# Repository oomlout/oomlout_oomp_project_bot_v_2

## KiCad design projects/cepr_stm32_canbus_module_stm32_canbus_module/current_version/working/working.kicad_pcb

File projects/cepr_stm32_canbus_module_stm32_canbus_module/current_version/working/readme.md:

# stm32_canbus_module
 
## summary 
* id: cepr_stm32_canbus_module_stm32_canbus_module
* user: cepr
* name: stm32_canbus_module
* board: stm32_canbus_module
* repo: https://github.com/cepr/stm32-canbus-module
* src_file_repo_kicad_pcb: stm32_canbus_module.kicad_pcb
* src_file_repo_kicad_pcb_link: https://github.com/cepr/stm32-canbus-module/tree/master/stm32_canbus_module.kicad_pcb
* src_file_repo_kicad_sch: stm32_canbus_module.kicad_sch
* src_file_repo_kicad_sch_link: https://github.com/cepr/stm32-canbus-module/tree/master/stm32_canbus_module.kicad_sch

* src_file_repo_sch: 
* src_file_repo_sch_link: https://github.com/cepr/stm32-canbus-module/tree/master/
* full details link: https://github.com/oomlout/oomlout_oomp_project_bot_v_2/tree/main/projects/cepr_stm32_canbus_module_stm32_canbus_module/current_version/working

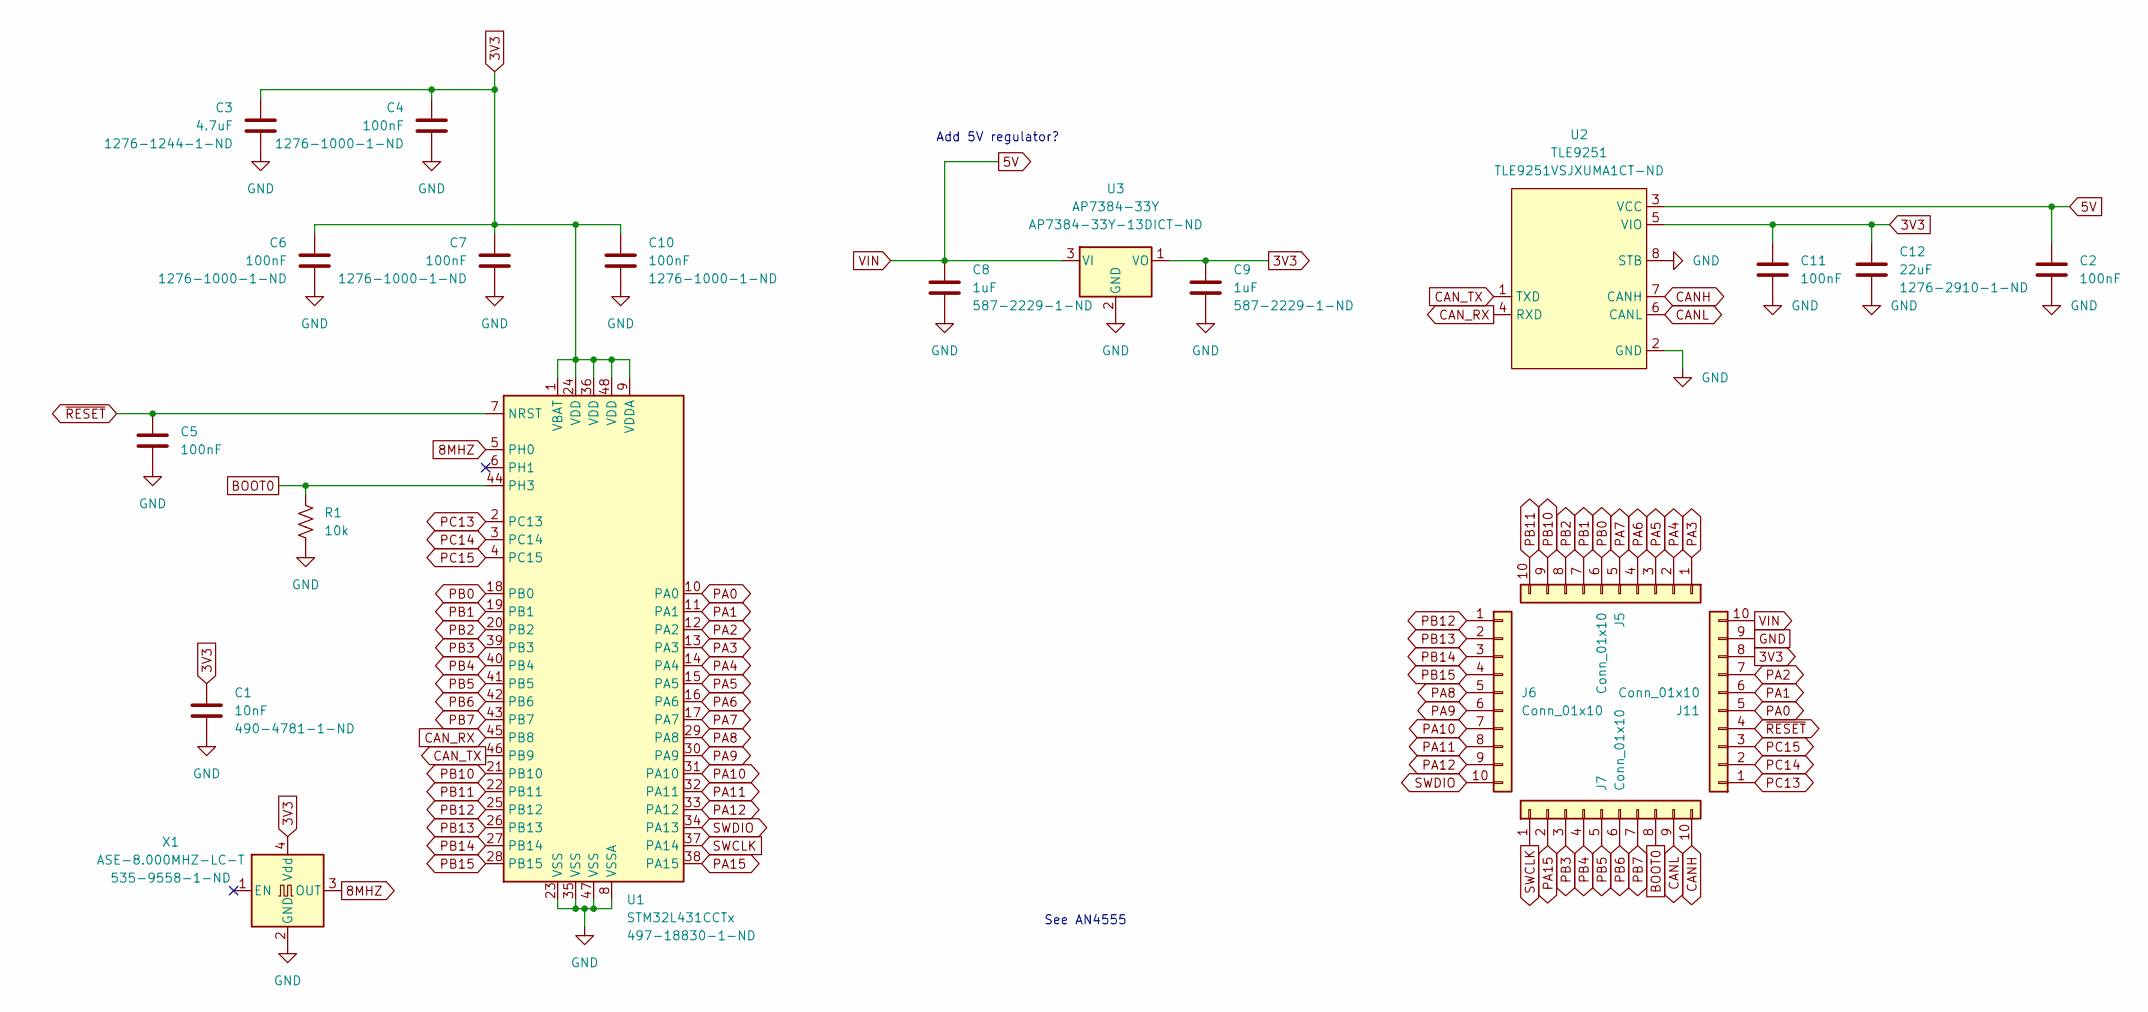
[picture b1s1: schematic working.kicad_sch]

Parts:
C1: 10nF; C_0603_1608Metric_Pad1.08x0.95mm_HandSolder; DigiKey 490-4781-1-ND
C2, C4, C5, C6, C7, C10, C11: 100nF; C_0603_1608Metric_Pad1.08x0.95mm_HandSolder; DigiKey 1276-1000-1-ND
C3: 4.7uF; C_0805_2012Metric_Pad1.18x1.45mm_HandSolder; DigiKey 1276-1244-1-ND
C8, C9: 1uF; C_0805_2012Metric_Pad1.18x1.45mm_HandSolder; DigiKey 587-2229-1-ND
C12: 22uF; C_0805_2012Metric_Pad1.18x1.45mm_HandSolder; DigiKey 1276-2910-1-ND
J5, J6, J7, J11: Conn_01x10; PinHeader_1x10_P2.54mm_Vertical
R1: 10k; R_0603_1608Metric_Pad0.98x0.95mm_HandSolder; DigiKey RNCP0603FTD10K0CT-ND
U1: STM32L431CCTx; LQFP-48_7x7mm_P0.5mm; DigiKey 497-18830-1-ND
U2: TLE9251; SOIC-8_3.9x4.9mm_P1.27mm; DigiKey TLE9251VSJXUMA1CT-ND
U3: AP7384-33Y; SOT-89-3; DigiKey AP7384-33Y-13DICT-ND
X1: ASE-8.000MHZ-LC-T; Oscillator_SMD_Abracon_ASE-4Pin_3.2x2.5mm_HandSoldering; DigiKey 535-9558-1-ND

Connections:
3V3: C1.1, C3.1, C4.1, C6.1, C7.1, C9.1, C10.1, C11.1, C12.1, J11.8, U1.1 (VBAT), U1.9 (VDDA), U1.24 (VDD), U1.36 (VDD), U1.48 (VDD), U2.5 (VIO), U3.1 (VO), X1.4 (Vdd)
5V: C2.1, C8.1, J11.10, U2.3 (VCC), U3.3 (VI)
8MHZ: U1.5 (PH0), X1.3 (OUT)
BOOT0: J7.8, R1.2, U1.44 (PH3)
CANH: J7.10, U2.7 (CANH)
CANL: J7.9, U2.6 (CANL)
CAN_RX: U1.45 (PB8), U2.4 (RXD)
CAN_TX: U1.46 (PB9), U2.1 (TXD)
GND: C1.2, C2.2, C3.2, C4.2, C5.2, C6.2, C7.2, C8.2, C9.2, C10.2, C11.2, C12.2, J11.9, R1.1, U1.8 (VSSA), U1.23 (VSS), U1.35 (VSS), U1.47 (VSS), U2.2 (GND), U2.8 (STB), U3.2 (GND), X1.2 (GND)
PA0: J11.5, U1.10 (PA0)
PA1: J11.6, U1.11 (PA1)
PA2: J11.7, U1.12 (PA2)
PA3: J5.1, U1.13 (PA3)
PA4: J5.2, U1.14 (PA4)
PA5: J5.3, U1.15 (PA5)
PA6: J5.4, U1.16 (PA6)
PA7: J5.5, U1.17 (PA7)
PA8: J6.5, U1.29 (PA8)
PA9: J6.6, U1.30 (PA9)
PA10: J6.7, U1.31 (PA10)
PA11: J6.8, U1.32 (PA11)
PA12: J6.9, U1.33 (PA12)
PA15: J7.2, U1.38 (PA15)
PB0: J5.6, U1.18 (PB0)
PB1: J5.7, U1.19 (PB1)
PB2: J5.8, U1.20 (PB2)
PB3: J7.3, U1.39 (PB3)
PB4: J7.4, U1.40 (PB4)
PB5: J7.5, U1.41 (PB5)
PB6: J7.6, U1.42 (PB6)
PB7: J7.7, U1.43 (PB7)
PB10: J5.9, U1.21 (PB10)
PB11: J5.10, U1.22 (PB11)
PB12: J6.1, U1.25 (PB12)
PB13: J6.2, U1.26 (PB13)
PB14: J6.3, U1.27 (PB14)
PB15: J6.4, U1.28 (PB15)
PC13: J11.1, U1.2 (PC13)
PC14: J11.2, U1.3 (PC14)
PC15: J11.3, U1.4 (PC15)
SWCLK: J7.1, U1.37 (PA14)
SWDIO: J6.10, U1.34 (PA13)
~RESET: C5.1, J11.4, U1.7 (NRST)

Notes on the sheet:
Add 5V regulator?
See AN4555

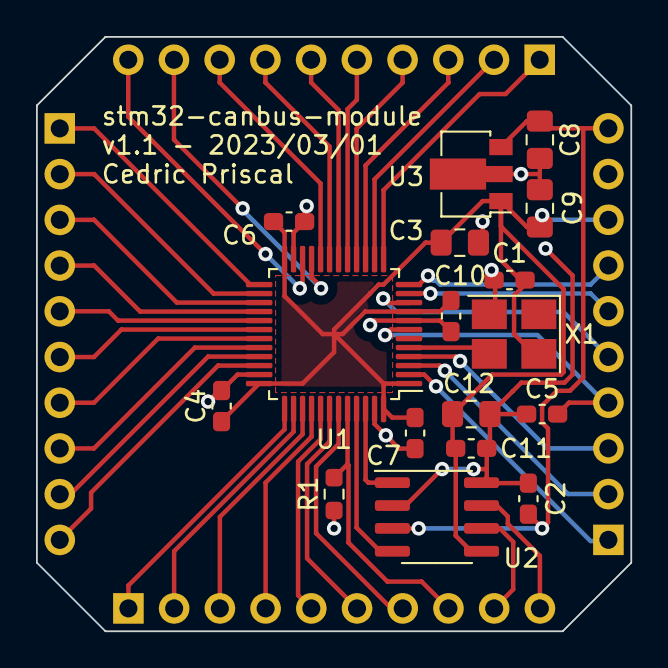
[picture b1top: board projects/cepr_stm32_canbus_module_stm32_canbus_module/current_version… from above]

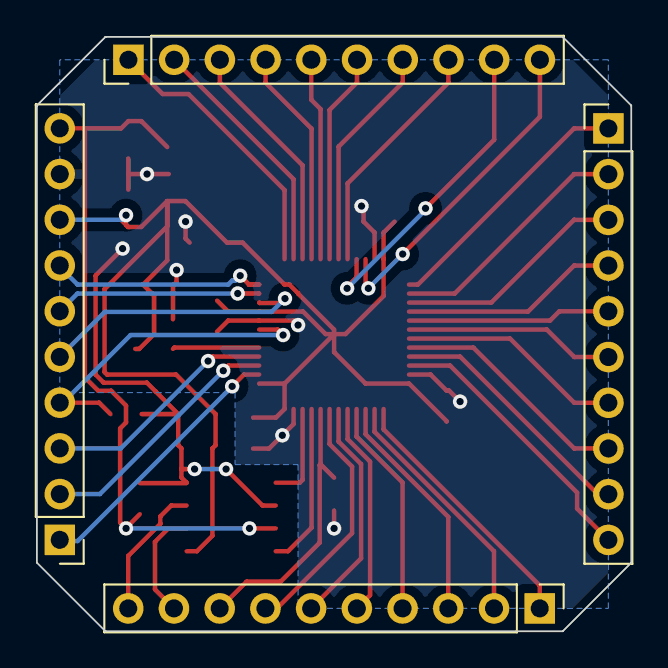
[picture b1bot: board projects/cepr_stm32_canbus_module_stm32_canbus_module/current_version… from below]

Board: 2 copper layers, 33.0 x 33.0 mm, 21 parts (4 on the bottom side), 43 nets.

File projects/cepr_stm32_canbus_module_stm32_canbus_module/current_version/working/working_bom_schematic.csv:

"Source:","C:\gh\oomlout_oomp_project_bot_v_2\projects\cepr_stm32_canbus_module_stm32_canbus_module\current_version\working\working.kicad_sch"
"Date:","28/09/2023 19:39:32"
"Tool:","Eeschema 7.0.6"
"Generator:","C:/Program Files/KiCad/7.0/bin/scripting/plugins/bom_csv_grouped_by_value_with_fp.py"
"Component Count:","21"
"Ref","Qnty","Value","Cmp name","Footprint","Description","Vendor","DNP"
"C1","1","10nF","C","Capacitor_SMD:C_0603_1608Metric_Pad1.08x0.95mm_HandSolder","Unpolarized capacitor","",""
"C2, C4, C5, C6, C7, C10, C11","7","100nF","C","Capacitor_SMD:C_0603_1608Metric_Pad1.08x0.95mm_HandSolder","Unpolarized capacitor","",""
"C3","1","4.7uF","C","Capacitor_SMD:C_0805_2012Metric_Pad1.18x1.45mm_HandSolder","Unpolarized capacitor","",""
"C8, C9","2","1uF","C","Capacitor_SMD:C_0805_2012Metric_Pad1.18x1.45mm_HandSolder","Unpolarized capacitor","",""
"C12","1","22uF","C","Capacitor_SMD:C_0805_2012Metric_Pad1.18x1.45mm_HandSolder","Unpolarized capacitor","",""
"J5, J6, J7, J11","4","Conn_01x10","Conn_01x10","Connector_PinHeader_2.54mm:PinHeader_1x10_P2.54mm_Vertical","Generic connector, single row, 01x10, script generated (kicad-library-utils/schlib/autogen/connector/)","",""
"R1","1","10k","R_US","Resistor_SMD:R_0603_1608Metric_Pad0.98x0.95mm_HandSolder","Resistor, US symbol","",""
"U1","1","STM32L431CCTx","STM32L431CCTx","Package_QFP:LQFP-48_7x7mm_P0.5mm","ARM Cortex-M4 MCU, 256KB flash, 64KB RAM, 80MHz, 1.71-3.6V, 38 GPIO, LQFP-48","",""
"U2","1","TLE9251","TLE9251","Package_SO:SOIC-8_3.9x4.9mm_P1.27mm","","",""
"U3","1","AP7384-33Y","AP7384-28Y","Package_TO_SOT_SMD:SOT-89-3","50mA Low Dropout Voltage Regulator, Fixed Output 2.8V, Wide Input Voltage Range 40V, SOT-89-3","",""
"X1","1","ASE-8.000MHZ-LC-T","ASE-xxxMHz","Oscillator:Oscillator_SMD_Abracon_ASE-4Pin_3.2x2.5mm_HandSoldering","3.3V CMOS SMD Crystal Clock Oscillator, Abracon","",""

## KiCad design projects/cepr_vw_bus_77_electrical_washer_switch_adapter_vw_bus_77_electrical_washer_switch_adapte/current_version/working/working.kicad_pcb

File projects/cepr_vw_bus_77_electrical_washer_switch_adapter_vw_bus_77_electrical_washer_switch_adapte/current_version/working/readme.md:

# vw_bus_77_electrical_washer_switch_adapter
 
## summary 
* id: cepr_vw_bus_77_electrical_washer_switch_adapter_vw_bus_77_electrical_washer_switch_adapte
* user: cepr
* name: vw_bus_77_electrical_washer_switch_adapter
* board: vw_bus_77_electrical_washer_switch_adapte
* repo: https://github.com/cepr/vw-bus-77-electrical-washer-switch-adapter
* src_file_repo_kicad_pcb: vw-bus-77-electrical-washer-switch-adapte.kicad_pcb
* src_file_repo_kicad_pcb_link: https://github.com/cepr/vw-bus-77-electrical-washer-switch-adapter/tree/master/vw-bus-77-electrical-washer-switch-adapte.kicad_pcb

* src_file_repo_sch: vw-bus-77-electrical-washer-switch-adapte.sch
* src_file_repo_sch_link: https://github.com/cepr/vw-bus-77-electrical-washer-switch-adapter/tree/master/vw-bus-77-electrical-washer-switch-adapte.sch
* full details link: https://github.com/oomlout/oomlout_oomp_project_bot_v_2/tree/main/projects/cepr_vw_bus_77_electrical_washer_switch_adapter_vw_bus_77_electrical_washer_switch_adapte/current_version/working

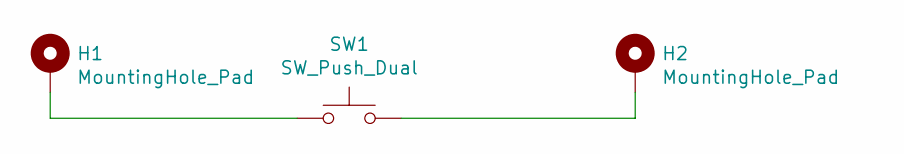
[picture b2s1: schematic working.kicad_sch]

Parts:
H1, H2: MountingHole_Pad; MountingHole_3.2mm_M3_Pad_Via
SW1: SW_Push_Dual; SW_PUSH_6mm

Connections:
unnamed: H1.1, SW1.1
unnamed: H2.1, SW1.2

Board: 2 copper layers, 3 parts (0 on the bottom side), 2 nets, no tracks yet.

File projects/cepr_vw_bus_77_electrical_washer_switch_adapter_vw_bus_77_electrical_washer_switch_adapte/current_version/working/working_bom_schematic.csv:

"Source:","C:\gh\oomlout_oomp_project_bot_v_2\projects\cepr_vw_bus_77_electrical_washer_switch_adapter_vw_bus_77_electrical_washer_switch_adapte\current_version\working\working.kicad_sch"
"Date:","28/09/2023 19:47:27"
"Tool:","Eeschema 7.0.6"
"Generator:","C:/Program Files/KiCad/7.0/bin/scripting/plugins/bom_csv_grouped_by_value_with_fp.py"
"Component Count:","3"
"Ref","Qnty","Value","Cmp name","Footprint","Description","Vendor","DNP"
"H1, H2","2","MountingHole_Pad","MountingHole_Pad","MountingHole:MountingHole_3.2mm_M3_Pad_Via","Mounting Hole with connection","",""
"SW1","1","SW_Push_Dual","SW_Push","Button_Switch_THT:SW_PUSH_6mm","Push button switch, generic, two pins","",""

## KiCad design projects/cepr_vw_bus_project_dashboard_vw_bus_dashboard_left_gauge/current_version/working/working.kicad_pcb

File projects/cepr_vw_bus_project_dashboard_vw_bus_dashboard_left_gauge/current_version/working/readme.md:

# vw_bus_project_dashboard
 
## summary 
* id: cepr_vw_bus_project_dashboard_vw_bus_dashboard_left_gauge
* user: cepr
* name: vw_bus_project_dashboard
* board: vw_bus_dashboard_left_gauge
* repo: https://github.com/cepr/vw-bus-project-dashboard
* src_file_repo_kicad_pcb: kicad/vw_bus_dashboard_left_gauge.kicad_pcb
* src_file_repo_kicad_pcb_link: https://github.com/cepr/vw-bus-project-dashboard/tree/master/kicad/vw_bus_dashboard_left_gauge.kicad_pcb

* src_file_repo_sch: kicad/vw_bus_dashboard_left_gauge.sch
* src_file_repo_sch_link: https://github.com/cepr/vw-bus-project-dashboard/tree/master/kicad/vw_bus_dashboard_left_gauge.sch
* full details link: https://github.com/oomlout/oomlout_oomp_project_bot_v_2/tree/main/projects/cepr_vw_bus_project_dashboard_vw_bus_dashboard_left_gauge/current_version/working

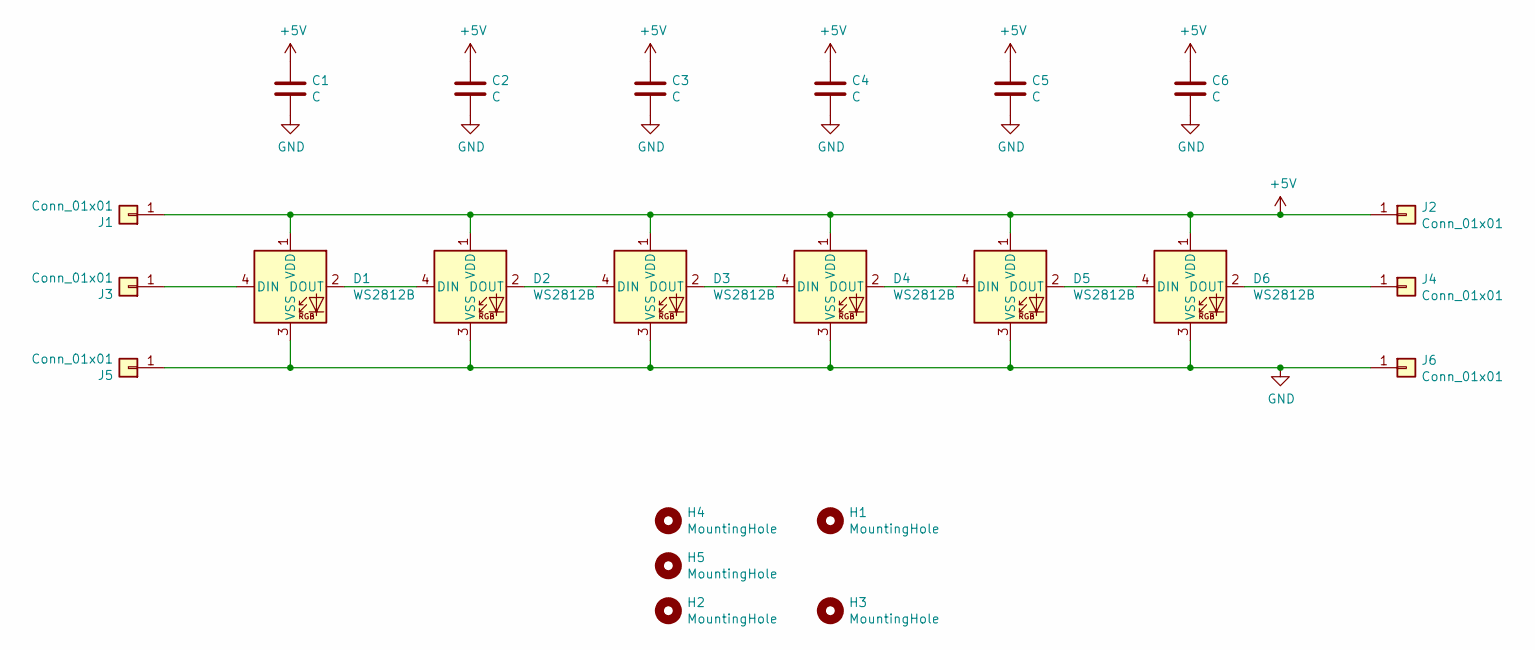
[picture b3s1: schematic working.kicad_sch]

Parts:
C1, C2, C3, C4, C5, C6: C; C_0603_1608Metric
D1, D2, D3, D4, D5, D6: WS2812B; LED_WS2812B_PLCC4_5.0x5.0mm_P3.2mm
H1, H3: MountingHole; MountingHole_5.3mm_M5
H2, H4, H5: MountingHole; MountingHole_3.2mm_M3
J1, J2, J3, J4, J5, J6: Conn_01x01; SolderWirePad_1x01_SMD_5x10mm

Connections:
+5V: C1.1, C2.1, C3.1, C4.1, C5.1, C6.1, D1.1 (VDD), D2.1 (VDD), D3.1 (VDD), D4.1 (VDD), D5.1 (VDD), D6.1 (VDD), J1.1, J2.1
GND: C1.2, C2.2, C3.2, C4.2, C5.2, C6.2, D1.3 (VSS), D2.3 (VSS), D3.3 (VSS), D4.3 (VSS), D5.3 (VSS), D6.3 (VSS), J5.1, J6.1
unnamed: D1.2 (DOUT), D2.4 (DIN)
unnamed: D1.4 (DIN), J3.1
unnamed: D2.2 (DOUT), D3.4 (DIN)
unnamed: D3.2 (DOUT), D4.4 (DIN)
unnamed: D4.2 (DOUT), D5.4 (DIN)
unnamed: D5.2 (DOUT), D6.4 (DIN)
unnamed: D6.2 (DOUT), J4.1

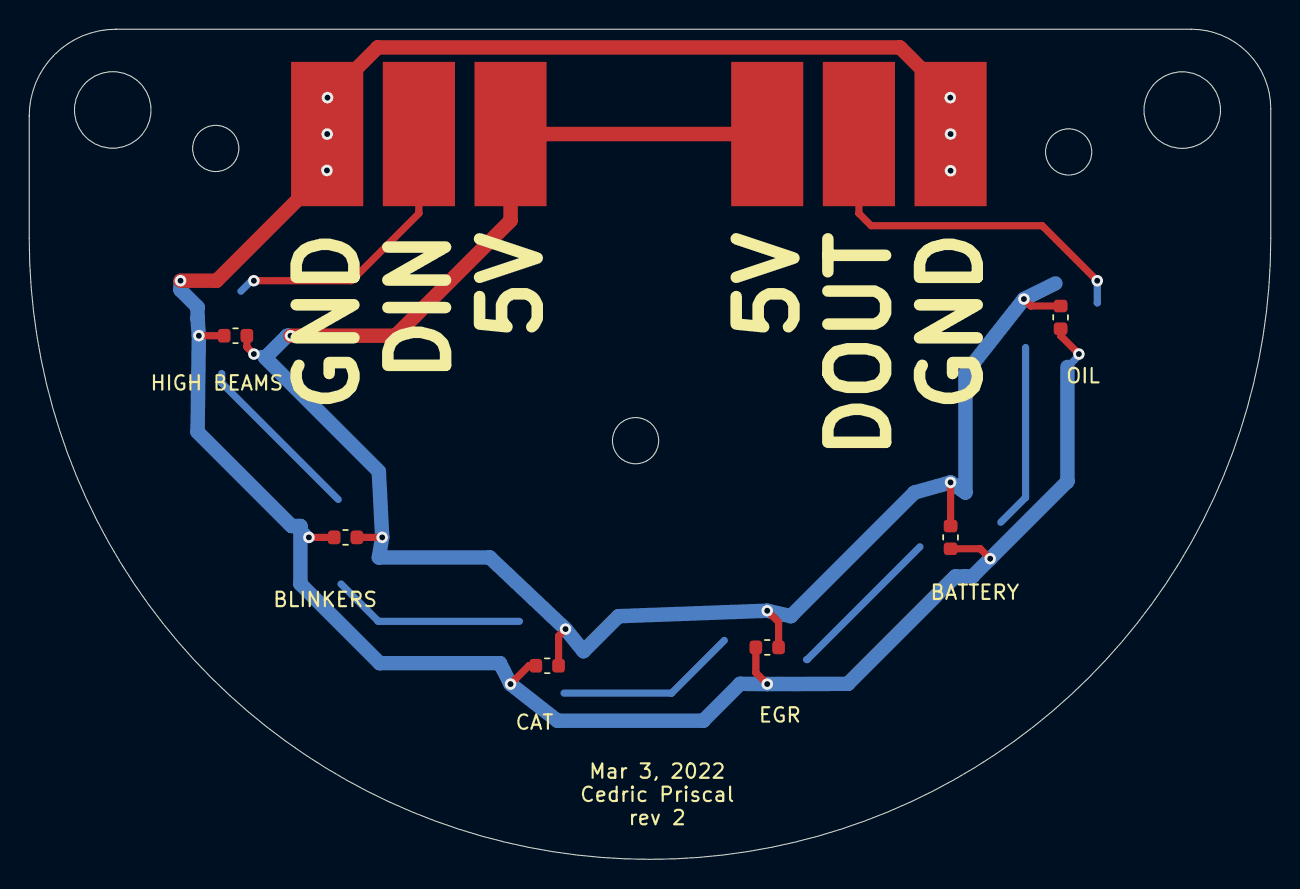
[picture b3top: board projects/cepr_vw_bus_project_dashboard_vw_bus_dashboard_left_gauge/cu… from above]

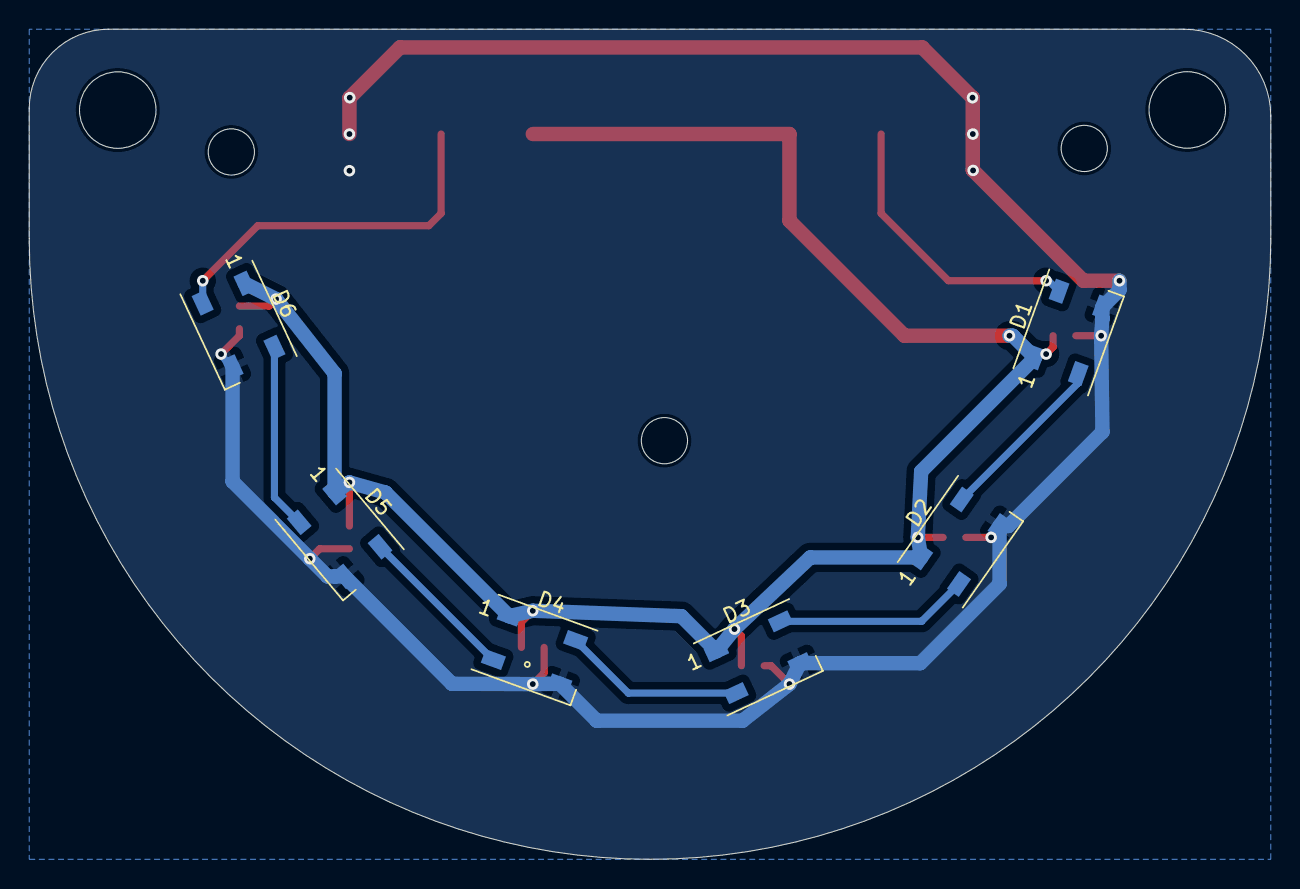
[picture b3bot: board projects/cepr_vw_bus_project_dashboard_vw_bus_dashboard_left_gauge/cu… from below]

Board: 2 copper layers, 86.0 x 57.5 mm, 23 parts (6 on the bottom side), 9 nets.

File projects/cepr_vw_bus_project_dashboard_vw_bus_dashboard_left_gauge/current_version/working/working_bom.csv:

"Id";"Designator";"Footprint";"Quantity";"Designation";"Supplier and ref";
1;"C1,C2,C3,C4,C5,C6";"C_0603_1608Metric";6;"C";;;
2;"D2,D3,D4,D5,D6,D1";"LED_WS2812B_PLCC4_5.0x5.0mm_P3.2mm";6;"WS2812B";;;

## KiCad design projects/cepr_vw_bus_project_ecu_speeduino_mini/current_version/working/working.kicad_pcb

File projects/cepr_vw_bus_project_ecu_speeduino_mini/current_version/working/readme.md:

# vw_bus_project_ecu
 
## summary 
* id: cepr_vw_bus_project_ecu_speeduino_mini
* user: cepr
* name: vw_bus_project_ecu
* board: speeduino_mini
* repo: https://github.com/cepr/vw-bus-project-ecu
* src_file_repo_kicad_pcb: hardware/speeduino_mini.kicad_pcb
* src_file_repo_kicad_pcb_link: https://github.com/cepr/vw-bus-project-ecu/tree/master/hardware/speeduino_mini.kicad_pcb

* src_file_repo_sch: 
* src_file_repo_sch_link: https://github.com/cepr/vw-bus-project-ecu/tree/master/
* full details link: https://github.com/oomlout/oomlout_oomp_project_bot_v_2/tree/main/projects/cepr_vw_bus_project_ecu_speeduino_mini/current_version/working

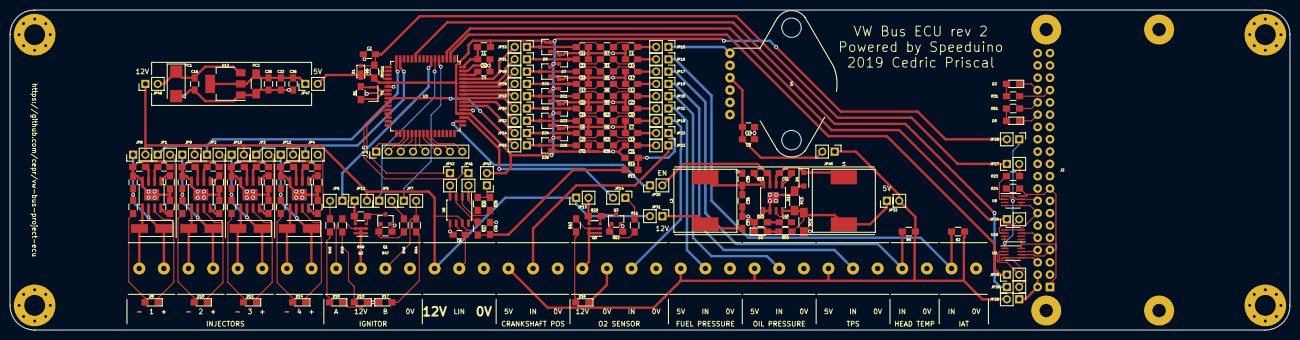
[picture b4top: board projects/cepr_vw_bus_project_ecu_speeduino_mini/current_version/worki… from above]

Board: 2 copper layers, 264.2 x 66.0 mm, 209 parts (0 on the bottom side), 147 nets.

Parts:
C1: 0.47nF 50V; C_0805_HandSoldering
C2: 4.7nF 100V; C_0805_HandSoldering
C4, C7, C12, C14, C16, C17, C19, C21, C22, C23, C33, C35, C36, C43: 0.1uF 50V; C_0805_HandSoldering
C6: 0.22nF 200V; C_0805_HandSoldering
C8, C13, C15, C18, C20, C32, C34, C41, C42: 0.22uF 50V; C_0805_HandSoldering
C9, C39, C46: 1uF 35V; C_0805_HandSoldering
C10: 10nF 100V; C_0805_HandSoldering
C11: 0.33uF 50V; C_0805_HandSoldering
C24, C26, C28, C30: 1nF 50V; C_0805_HandSoldering
C25, C27, C29, C31: 22uF 16V; C_0805_HandSoldering
C37, C38: 22uF 25V; C_0805_HandSoldering
C40: 22nF 50V; C_0805_HandSoldering
D1: MSS1P3L-M3/89A; MicroSMP
D2, D17, D18: LED BLUE 10mA 3V; LED_0805_HandSoldering
D3, D16, D19: LED GREEN 2.5mA 2.7V; LED_0805_HandSoldering
D4: D_Schottky; D_SOD-123F
D5, D8, D10, D12, D14: LED RED 10mA 1.9V; LED_0805_HandSoldering
D6, D7, D20, D21, D22, D23, D24, D25, D26: NUP1301,215; SOT-23
D9, D11, D13, D15: B340A-13-F; D_SMA_Handsoldering
H1, H2, H3, H4: MountingHole; MountingHole_4.3mm_M4_Pad_Via
J1: O2; ED120_4DS
J2: Raspberry_Pi_2_3; RaspberryPi_uHAT
J3: TPS; ED120_3DS
J4: IAT; ED120_2DS
J5: head temperature; ED120_2DS
J6: crankshaft position sensor; ED120_3DS
J7, J8, J9, J10: Injector; ED120_2DS
J11: Ignitor Pack; ED120_4DS
J12: oil pressure; ED120_3DS
J13: fuel pressure; ED120_3DS
J14: power; ED120_3DS
J15: Conn_01x08_Female; Pin_Header_Straight_1x08_Pitch2.54mm
JP1, JP2, JP3, JP4, JP5, JP6, JP7, JP8, JP9, JP10, JP11, JP12, JP13, JP14, JP15, JP16, JP17, JP18, JP19, JP20, JP21, JP22, JP23, JP24, JP25, JP26, JP27, JP28, JP29, JP30, JP31, JP32, JP39, JP40, JP41, JP42, JP43, JP45, JP46, JP47, JP49, JP50, JP51, JP52, JP53, JP54, JP55: Jumper; Pin_Header_Straight_1x02_Pitch2.54mm
L1: 10uH; L_0805_HandSoldering
L3, L4: 47uH; BOURNS_SRR1260
PC1: 47uF; CP_Tantalum_Case-C_EIA-6032-28_Reflow
PC2, PC3, PC4: 47uF 10V; C_1206_HandSoldering
Q1, Q3: 2N7002; SOT-23
Q2, Q5: SQ3457EV; TSOP-6_1.65x3.05mm_Pitch0.95mm
R1: 1M; R_0805_HandSoldering
R2, R4: 2.49k; R_0805_HandSoldering
R3, R5, R6, R8, R9, R10, R15, R26: 470; R_0805_HandSoldering
R7: 750; R_0805_HandSoldering
R11, R23, R46: 150; R_0805_HandSoldering
R12, R16, R17, R21, R24, R29, R35, R39, R47, R48: 10k; R_0805_HandSoldering
R13: 3.9k; R_0805_HandSoldering
R14, R19, R33, R37, R41: 1k; R_0805_HandSoldering
R18, R22, R36, R40: 47.5k; R_0805_HandSoldering
R20, R34, R38, R42: 26.1k; R_0805_HandSoldering
R25: 22k; R_0805_HandSoldering
R27, R28: 33k; R_0805_HandSoldering
R30: 4k7; R_0805_HandSoldering
R31, R44, R45: 200; R_0805_HandSoldering
R43, R49: 3.74k; R_0805_HandSoldering
R50: 910; R_0805_HandSoldering
R51: 309; R_0805_HandSoldering
RN5A1: 10k; R_0805_HandSoldering
U3: ATmega2561-16AU; TQFP-64_14x14mm_Pitch0.8mm
U4: MPX4250AP1; xP_01ASB0907B
U5, U9, U10: SN74LVC2T45MDCTTEP; SSOP-8_2.95x2.8mm_Pitch0.65mm
U7, U13, U14, U15: DRV103H; TI_SO-PowerPAD-8
U8: MCP2003B; SOIC-8_3.9x4.9mm_Pitch1.27mm
U11: TLE8366; SOIC-8-1EP_3.9x4.9mm_Pitch1.27mm
U12: LD1117S50TR_SOT223; SOT-223-3_TabPin2
Y1: CSTCE16M0V53-R0; Resonator_SMD_Murata-3pin_3.2x1.3mm

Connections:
+5VA: J3.1, J6.1, J12.1, J13.1, JP29.2, JP32.2, JP45.1, R2.1, R4.1
+5VD: D1.1, D6.2, D7.2, D20.2, D21.2, D22.2, D23.2, D24.2, D25.2, D26.2, JP28.2, JP43.2, JP47.2, L1.1, RN5A1.1, U3.21, U3.52
+12V: C46.1, J14.1, JP8.2, JP9.2, JP10.2, JP11.2, JP12.2, JP13.1, JP31.2, JP46.1, R13.1, R27.2, U8.7
/Crankshaft pos sensor/IN: J6.2, JP22.1
/Fuel Pressure/IN: J13.2, JP21.1
/Head Temperature Sensor/IN: J5.1, JP17.1, R4.2
/Ignitor/+12V: JP12.1, Q2.4, R48.1
/Ignitor/EN: JP5.2, R46.2
/Ignitor/IN1: J11.1, JP6.2, R45.2
/Ignitor/IN2: J11.3, JP7.2, R44.2
/Ignitor/sheet5CF8D1B3/OUT: J11.2, Q2.1, Q2.2, Q2.5, Q2.6, R49.2
/Injector 1/+12V: C25.1, D9.1, J7.1, JP8.1, R19.1, U7.6
/Injector 1/INJ_CMD: JP1.2, R17.1, U7.8
/Injector 2/+12V: C27.1, D11.1, J8.1, JP9.1, R33.1, U13.6
/Injector 2/INJ_CMD: JP2.2, R21.1, U13.8
/Injector 3/+12V: C29.1, D13.1, J9.1, JP10.1, R37.1, U14.6
/Injector 3/INJ_CMD: JP3.2, R35.1, U14.8
/Injector 4/+12V: C31.1, D15.1, J10.1, JP11.1, R41.1, U15.6
/Injector 4/INJ_CMD: JP4.2, R39.1, U15.8
/Intake Air Temperature Sensor/IN: J4.1, JP16.1, R2.2
/MAP Sensor/+5V: C9.1, C10.1, JP45.2, U4.3
/MCU/A0: C11.1, D6.3, JP53.1, R7.1
/MCU/A1: C15.1, D7.3, JP51.1, R3.1
/MCU/A2: C18.1, D20.3, JP49.1, R5.1
/MCU/A3: C13.1, D21.3, JP39.1, R8.1
/MCU/A4: C32.1, D22.3, JP40.1, R9.1
/MCU/A5: C34.1, D23.3, JP50.1, R10.1
/MCU/A6: C8.1, D24.3, JP52.1, R6.1
/MCU/A7: C20.1, D25.3, JP54.1, R15.1
/MCU/ATMEGA regulator/AVCC: C43.1, L1.2, U3.64
/MCU/INT0: C42.1, D26.3, JP55.1, R26.1
/MCU/LIN: C6.1, J14.2, U8.6
/MCU/OC1A: JP3.1, JP4.1, U3.15
/MCU/OC1B: JP1.1, JP2.1, U3.16
/MCU/OC3A: JP7.1, U3.5
/MCU/OC3B: JP5.1, U3.6
/MCU/OC3C: JP6.1, U3.7
/MCU/PA0: JP14.2, U3.51
/MCU/PA1: JP30.1, U3.50
/MCU/RESET: C2.1, D1.2, JP27.1, RN5A1.2, U3.20
/MCU/RXD0: JP25.1, U3.2
/MCU/SCK: JP26.1, U3.11
/MCU/TXD0: JP24.1, U3.3
/MCU/sheet5D16F277/+5V: JP43.1, R28.2, R30.1
/MCU/sheet5D16F277/RXD: JP41.2, R30.2, U8.1
/MCU/sheet5D16F277/TXD: JP42.2, U8.4
/O2 Sensor Power/+12V: JP13.2, Q5.4, R29.1
/O2 Sensor Power/EN: JP14.1, R11.2
/O2 Sensor Power/OUT: J1.1, Q5.1, Q5.2, Q5.5, Q5.6, R43.2
/O2 Sensor/IN: J1.3, JP18.1
/Oil Pressure Sensor/IN: J12.2, JP20.1
/Power/+5V: JP32.1, L4.2, PC3.1, PC4.1, R50.2, U11.4
/Power/+12V: C37.1, JP31.1, L3.1
/Power/EN: JP30.2, R16.1, U11.7
/Raspberry Pi Zero W/+5VA: J2.2, J2.4, JP29.1
/Raspberry Pi Zero W/+5VD: JP28.1, U5.1, U9.1, U10.7, U10.8
/Raspberry Pi Zero W/ATMEGA_RESET: JP27.2, R23.2
/Raspberry Pi Zero W/RXD_PDO: JP24.2, U10.6
/Raspberry Pi Zero W/SCK: JP26.2, U5.3
/Raspberry Pi Zero W/TXD_PDI: JP25.2, U5.2
/Throttle Position Sensor /IN: J3.2, JP19.1
GND: C1.2, C2.2, C4.2, C6.2, C7.2, C8.2, C9.2, C10.2, C11.2, C12.2, C13.2, C14.2, C15.2, C16.2, C17.2, C18.2, C19.2, C20.2, C21.2, C22.2, C23.2, C24.2, C25.2, C26.2, C27.2, C28.2, C29.2, C30.2, C31.2, C32.2, C33.2, C34.2, C35.2, C36.2, C37.2, C38.2, C39.2, C42.2, C43.2, C46.2, D2.1, D3.1, D4.2, D5.1, D6.1, D7.1, D16.1, D17.1, D18.1, D19.1, D20.1, D21.1, D22.1, D23.1, D24.1, D25.1, D26.1, J1.2, J1.4, J2.6, J2.14, J2.20, J2.30, J2.34, J3.3, J4.2, J5.2, J6.3, J11.4, J12.3, J13.3, J14.3, PC1.2, PC2.2, PC3.2, PC4.2, Q1.2, Q3.2, R12.2, R14.2, R17.2, R18.2, R20.2, R21.2, R22.2, R25.2, R34.2, R35.2, R36.2, R38.2, R39.2, R40.2, R42.2, R47.2, U3.22, U3.53, U3.63, U4.2, U5.4, U5.5, U7.4, U7.9, U8.5, U9.4, U9.5, U9.6, U10.4, U10.5, U11.1, U11.2, U11.9, U12.1, U13.4, U13.9, U14.4, U14.9, U15.4, U15.9, Y1.2
unnamed: C1.1, JP15.2, R7.2
unnamed: C4.1, U3.62
unnamed: C7.1, JP18.2, R6.2
unnamed: C12.1, JP19.2, R8.2
unnamed: C14.1, JP16.2, R3.2
unnamed: C16.1, JP46.2, PC1.1, U12.3
unnamed: C17.1, JP17.2, R5.2
unnamed: C19.1, JP23.2, R15.2
unnamed: C21.1, JP22.2, R26.2
unnamed: C22.1, C35.1, C36.1, JP47.1, PC2.1, U12.2
unnamed: C23.1, JP20.2, R9.2
unnamed: C24.1, U7.2
unnamed: C26.1, U13.2
unnamed: C28.1, U14.2
unnamed: C30.1, U15.2
unnamed: C33.1, JP21.2, R10.2
unnamed: C38.1, C39.1, L3.2, R16.2, U11.8
unnamed: C40.1, U11.3
unnamed: C40.2, R25.1
unnamed: C41.1, U11.5
unnamed: C41.2, D4.1, L4.1, U11.6
unnamed: D2.2, R31.1
unnamed: D3.2, R50.1
unnamed: D5.2, R51.1
unnamed: D8.1, U7.7
unnamed: D8.2, R19.2
unnamed: D9.2, J7.2, U7.5
unnamed: D10.1, U13.7
unnamed: D10.2, R33.2
unnamed: D11.2, J8.2, U13.5
unnamed: D12.1, U14.7
unnamed: D12.2, R37.2
unnamed: D13.2, J9.2, U14.5
unnamed: D14.1, U15.7
unnamed: D14.2, R41.2
unnamed: D15.2, J10.2, U15.5
unnamed: D16.2, R43.1
unnamed: D17.2, R44.1
unnamed: D18.2, R45.1
unnamed: D19.2, R49.1
unnamed: J2.1, J2.17, R24.2, U5.8, U9.8, U10.1
unnamed: J2.7, U5.6
unnamed: J2.8, U5.7
unnamed: J2.10, U10.3
unnamed: J2.16, R24.1, U9.7
unnamed: J2.32, R51.2
unnamed: J2.33, R31.2
unnamed: J15.1, U3.35
unnamed: J15.2, U3.36
unnamed: J15.3, U3.37
unnamed: J15.4, U3.38
unnamed: J15.5, U3.39
unnamed: J15.6, U3.40
unnamed: J15.7, U3.41
unnamed: J15.8, U3.42
unnamed: JP15.1, U4.1
unnamed: JP23.1, R13.2, R14.1
unnamed: JP39.2, U3.58
unnamed: JP40.2, U3.57
unnamed: JP41.1, U3.27
unnamed: JP42.1, U3.28
unnamed: JP49.2, U3.59
unnamed: JP50.2, U3.56
unnamed: JP51.2, U3.60
unnamed: JP52.2, U3.55
unnamed: JP53.2, U3.61
unnamed: JP54.2, U3.54
unnamed: JP55.2, U3.25
unnamed: Q1.1, R46.1, R47.1
unnamed: Q1.3, Q2.3, R48.2
unnamed: Q3.1, R11.1, R12.1
unnamed: Q3.3, Q5.3, R29.2
unnamed: R1.1, U3.24, Y1.1
unnamed: R1.2, U3.23, Y1.3
unnamed: R18.1, U7.3
unnamed: R20.1, U7.1
unnamed: R22.1, U13.3
unnamed: R23.1, U9.2
unnamed: R27.1, U8.3
unnamed: R28.1, U8.2
unnamed: R34.1, U13.1
unnamed: R36.1, U14.3
unnamed: R38.1, U14.1
unnamed: R40.1, U15.3
unnamed: R42.1, U15.1

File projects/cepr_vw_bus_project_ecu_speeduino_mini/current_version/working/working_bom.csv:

"Id";"Designator";"Footprint";"Quantity";"Designation";"Supplier and ref";
1;"JP8,JP40,JP21,JP46,JP42,JP53,JP22,JP52,JP50,JP55,JP31,JP32,JP15,JP17,JP47,JP30,JP26,JP54,JP23,JP14,JP13,JP41,JP11,JP12,JP24,JP25,JP27,JP28,JP29,JP39,JP43,JP49,JP1,JP2,JP4,JP5,JP6,JP7,JP9,JP10,JP45,JP16,JP3,JP51,JP20,JP19,JP18";"Pin_Header_Straight_1x02_Pitch2.54mm";47;"Jumper";;;
2;"PC3,PC2,PC4";"C_1206_HandSoldering";3;"47uF 10V";;;
3;"C38,C37";"C_0805_HandSoldering";2;"22uF 25V";;;
4;"C15,C20,C32,C34,C41,C42,C8,C13,C18";"C_0805_HandSoldering";9;"0.22uF 50V";;;
5;"R50";"R_0805_HandSoldering";1;"910";;;
6;"R51";"R_0805_HandSoldering";1;"309";;;
7;"C43,C36,C21,C23,C33,C7,C16,C22,C35,C4,C12,C14,C17,C19";"C_0805_HandSoldering";14;"0.1uF 50V";;;
8;"R31,R44,R45";"R_0805_HandSoldering";3;"200";;;
9;"PC1";"CP_Tantalum_Case-C_EIA-6032-28_Reflow";1;"47uF";;;
10;"U12";"SOT-223-3_TabPin2";1;"LD1117S50TR_SOT223";;;
11;"U8";"SOIC-8_3.9x4.9mm_Pitch1.27mm";1;"MCP2003B";;;
12;"R11,R23,R46";"R_0805_HandSoldering";3;"150";;;
13;"D3,D16,D19";"LED_0805_HandSoldering";3;"LED GREEN 2.5mA 2.7V";;;
14;"D2,D17,D18";"LED_0805_HandSoldering";3;"LED BLUE 10mA 3V";;;
15;"R30";"R_0805_HandSoldering";1;"4k7";;;
16;"C1";"C_0805_HandSoldering";1;"0.47nF 50V";;;
17;"U4";"xP_01ASB0907B";1;"MPX4250AP1";;;
18;"C39,C46,C9";"C_0805_HandSoldering";3;"1uF 35V";;;
19;"C40";"C_0805_HandSoldering";1;"22nF 50V";;;
20;"R1";"R_0805_HandSoldering";1;"1M";;;
21;"R2,R4";"R_0805_HandSoldering";2;"2.49k";;;
22;"R3,R5,R15,R8,R9,R10,R6,R26";"R_0805_HandSoldering";8;"470";;;
23;"R7";"R_0805_HandSoldering";1;"750";;;
24;"R13";"R_0805_HandSoldering";1;"3.9k";;;
25;"R14,R19,R33,R37,R41";"R_0805_HandSoldering";5;"1k";;;
26;"R16,R12,R17,R21,R35,R39,R24,R29,R47,R48,RN5A1";"R_0805_HandSoldering";11;"10k";;;
27;"R28,R27";"R_0805_HandSoldering";2;"33k";;;
28;"D5,D8,D10,D12,D14";"LED_0805_HandSoldering";5;"LED RED 10mA 1.9V";;;
29;"D4";"D_SOD-123F";1;"D_Schottky";;;
30;"L4,L3";"BOURNS_SRR1260";2;"47uH";;;
31;"J14";"ED120_3DS";1;"power";;;
32;"J6";"ED120_3DS";1;"crankshaft position sensor";;;
33;"U3";"TQFP-64_14x14mm_Pitch0.8mm";1;"ATmega2561-16AU";;;
34;"Q5,Q2";"TSOP-6_1.65x3.05mm_Pitch0.95mm";2;"SQ3457EV";;;
35;"Q3,Q1";"SOT-23";2;"2N7002";;;
36;"J13";"ED120_3DS";1;"fuel pressure";;;
37;"J12";"ED120_3DS";1;"oil pressure";;;
38;"J1";"ED120_4DS";1;"O2";;;
39;"D1";"MicroSMP";1;"MSS1P3L-M3/89A";;;
40;"Y1";"Resonator_SMD_Murata-3pin_3.2x1.3mm";1;"CSTCE16M0V53-R0";;;
41;"J4";"ED120_2DS";1;"IAT";;;
42;"J5";"ED120_2DS";1;"head temperature";;;
43;"J3";"ED120_3DS";1;"TPS";;;
44;"J2";"RaspberryPi_uHAT";1;"Raspberry_Pi_2_3";;;
45;"C24,C26,C28,C30";"C_0805_HandSoldering";4;"1nF 50V";;;
46;"C27,C29,C31,C25";"C_0805_HandSoldering";4;"22uF 16V";;;
47;"D9,D11,D13,D15";"D_SMA_Handsoldering";4;"B340A-13-F";;;
48;"R18,R22,R36,R40";"R_0805_HandSoldering";4;"47.5k";;;
49;"R20,R34,R38,R42";"R_0805_HandSoldering";4;"26.1k";;;
50;"U7,U13,U14,U15";"TI_SO-PowerPAD-8";4;"DRV103H";;;
51;"C6";"C_0805_HandSoldering";1;"0.22nF 200V";;;
52;"D6,D23,D25,D7,D24,D22,D20,D21,D26";"SOT-23";9;"NUP1301,215";;;
53;"U5,U10,U9";"SSOP-8_2.95x2.8mm_Pitch0.65mm";3;"SN74LVC2T45MDCTTEP";;;
54;"U11";"SOIC-8-1EP_3.9x4.9mm_Pitch1.27mm";1;"TLE8366";;;
55;"L1";"L_0805_HandSoldering";1;"10uH";;;
56;"R25";"R_0805_HandSoldering";1;"22k";;;
57;"J7,J8,J9,J10";"ED120_2DS";4;"Injector";;;
58;"J11";"ED120_4DS";1;"Ignitor Pack";;;
59;"R43,R49";"R_0805_HandSoldering";2;"3.74k";;;
60;"C2";"C_0805_HandSoldering";1;"4.7nF 100V";;;
61;"C10";"C_0805_HandSoldering";1;"10nF 100V";;;
62;"C11";"C_0805_HandSoldering";1;"0.33uF 50V";;;
63;"J15";"Pin_Header_Straight_1x08_Pitch2.54mm";1;"Conn_01x08_Female";;;

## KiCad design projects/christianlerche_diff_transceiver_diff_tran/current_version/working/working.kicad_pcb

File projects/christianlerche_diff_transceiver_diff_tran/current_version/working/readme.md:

# diff_transceiver
 
## summary 
* id: christianlerche_diff_transceiver_diff_tran
* user: christianlerche
* name: diff_transceiver
* board: diff_tran
* repo: https://github.com/ChristianLerche/Diff_transceiver
* src_file_repo_kicad_pcb: diff_tran.kicad_pcb
* src_file_repo_kicad_pcb_link: https://github.com/ChristianLerche/Diff_transceiver/tree/master/diff_tran.kicad_pcb

* src_file_repo_sch: diff_tran.sch
* src_file_repo_sch_link: https://github.com/ChristianLerche/Diff_transceiver/tree/master/diff_tran.sch
* full details link: https://github.com/oomlout/oomlout_oomp_project_bot_v_2/tree/main/projects/christianlerche_diff_transceiver_diff_tran/current_version/working  

## schematic  
  
[schematic (pdf)](working_schematic.pdf) 

## pcb  

[board (pdf)](working.pdf)  

## working_bom
| Id | Designator | Footprint | Quantity | Designation | Supplier and ref |  | None | 
| --- | --- | --- | --- | --- | --- | --- | --- | 
| 1 | C1,C2,C3,C5 | C_0603 | 4 | 100nF |  |  | [''] | 
| 2 | C4 | Tantalum_Case-A_EIA-3216-18_Reflow | 1 | 10uF |  |  | [''] | 
| 3 | D1 | LED_0603 | 1 | RED_LED |  |  | [''] | 
| 4 | IC1,IC4,IC2,IC3 | SOIC-8-N | 4 | SN65LVDM176 |  |  | [''] | 
| 5 | J1,J2,J7,J8,J9,J12,J3,J4,J5,J6,J10,J11 | Lerche_2PsolderJumper | 12 | SOLDER_JUMPER |  |  | [''] | 
| 6 | P2 | Pin_Header_Straight_2x05 | 1 | CONN_02X05 |  |  | [''] | 
| 7 | R1 | R_0603 | 1 | 330 |  |  | [''] | 
| 8 | R2,R5,R3,R4 | R_0603 | 4 | 100 |  |  | [''] | 
| 9 | ,,,,,,,,,,,,,,,,,,,,,,,,,,,,,, | Lerche_via_0.35_GND_MaskOver | 31 |  |  |  | [''] | 
| 10 | P1 | Lerche_2x3p_2.54mm_PCBedge | 1 | CONN_02X03 |  |  | [''] | 

## bom_schematic
| Ref | Qnty | Value | Cmp name | Footprint | Description | Vendor | DNP | 
| --- | --- | --- | --- | --- | --- | --- | --- | 
| C1, C2, C3, C5 | 4 | 100nF | C | Capacitors_SMD:C_0603 |  |  |  | 
| C4 | 1 | 10uF | CP | Capacitors_Tantalum_SMD:Tantalum_Case-A_EIA-3216-18_Reflow |  |  |  | 
| D1 | 1 | RED_LED | LED | LEDs:LED_0603 |  |  |  | 
| IC1, IC2, IC3, IC4 | 4 | SN65LVDM176 | SN65LVDM176 | SMD_Packages:SOIC-8-N |  |  |  | 
| J1, J2, J3, J4, J5, J6, J7, J8, J9, J10, J11, J12 | 12 | SOLDER_JUMPER | SOLDER_JUMPER | LercheTech:Lerche_2PsolderJumper |  |  |  | 
| P1 | 1 | CONN_02X03 | CONN_02X03 | Pin_Headers:Pin_Header_Straight_2x03 |  |  |  | 
| P2 | 1 | CONN_02X05 | CONN_02X05 | Pin_Headers:Pin_Header_Straight_2x05 |  |  |  | 
| R1 | 1 | 330 | R | Resistors_SMD:R_0603 |  |  |  | 
| R2, R3, R4, R5 | 4 | 100 | R | Resistors_SMD:R_0603 |  |  |  |

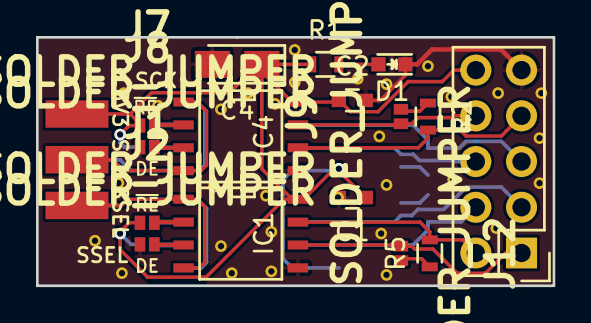
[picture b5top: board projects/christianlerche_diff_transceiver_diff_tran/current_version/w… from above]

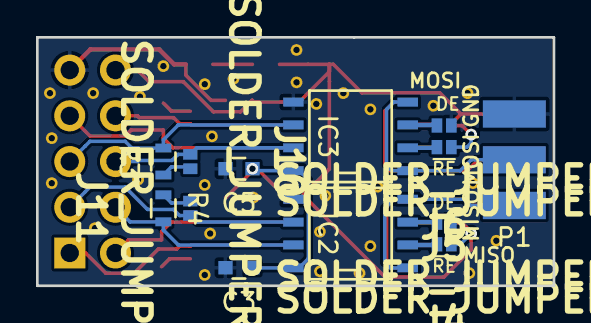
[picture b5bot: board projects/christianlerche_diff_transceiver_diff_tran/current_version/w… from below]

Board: 2 copper layers, 28.7 x 13.8 mm, 29 parts (13 on the bottom side), 27 nets.

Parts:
C1, C2, C3, C5: 100nF; C_0603
C4: 10uF; Tantalum_Case-A_EIA-3216-18_Reflow
D1: RED_LED; LED_0603
IC1, IC2, IC3, IC4: SN65LVDM176; SOIC-8-N
J1, J2, J3, J4, J5, J6, J7, J8, J9, J10, J11, J12: SOLDER_JUMPER; Lerche_2PsolderJumper
P1: CONN_02X03; Lerche_2x3p_2.54mm_PCBedge
P2: CONN_02X05; Pin_Header_Straight_2x05
R1: 330; R_0603
R2, R3, R4, R5: 100; R_0603

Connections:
+3V3: C1.1, C2.1, C3.1, C4.1, C5.1, IC1.8, IC2.8, IC3.8, IC4.8, J1.1, J3.1, J5.1, J7.1, P1.6, P2.10, R1.1
GND: C1.2, C2.2, C3.2, C4.2, C5.2, D1.1, IC1.5, IC2.5, IC3.5, IC4.5, J2.1, J4.1, J6.1, J8.1, P1.5, P2.9
MISO: IC2.1, IC2.4, P1.1
MOSI: IC3.1, IC3.4, P1.3
unnamed: D1.2, R1.2
unnamed: IC1.2, J1.2
unnamed: IC1.3, J2.2
unnamed: IC1.6, J12.1, P2.1
unnamed: IC1.7, P2.2, R5.2
unnamed: IC2.2, J3.2
unnamed: IC2.3, J4.2
unnamed: IC2.6, J11.1, P2.3
unnamed: IC2.7, P2.4, R4.2
unnamed: IC3.2, J5.2
unnamed: IC3.3, J6.2
unnamed: IC3.6, P2.5, R3.2
unnamed: IC3.7, J10.1, P2.6
unnamed: IC4.2, J7.2
unnamed: IC4.3, J8.2
unnamed: IC4.6, P2.7, R2.2
unnamed: IC4.7, J9.1, P2.8
unnamed: J9.2, R2.1
unnamed: J10.2, R3.1
unnamed: J11.2, R4.1
unnamed: J12.2, R5.1
SCK: IC4.1, IC4.4, P1.4
SSEL: IC1.1, IC1.4, P1.2

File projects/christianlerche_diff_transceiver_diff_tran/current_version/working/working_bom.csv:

"Id";"Designator";"Footprint";"Quantity";"Designation";"Supplier and ref";
1;"C1,C2,C3,C5";"C_0603";4;"100nF";;;
2;"C4";"Tantalum_Case-A_EIA-3216-18_Reflow";1;"10uF";;;
3;"D1";"LED_0603";1;"RED_LED";;;
4;"IC1,IC4,IC2,IC3";"SOIC-8-N";4;"SN65LVDM176";;;
5;"J1,J2,J7,J8,J9,J12,J3,J4,J5,J6,J10,J11";"Lerche_2PsolderJumper";12;"SOLDER_JUMPER";;;
6;"P2";"Pin_Header_Straight_2x05";1;"CONN_02X05";;;
7;"R1";"R_0603";1;"330";;;
8;"R2,R5,R3,R4";"R_0603";4;"100";;;
9;",,,,,,,,,,,,,,,,,,,,,,,,,,,,,,";"Lerche_via_0.35_GND_MaskOver";31;"";;;
10;"P1";"Lerche_2x3p_2.54mm_PCBedge";1;"CONN_02X03";;;
